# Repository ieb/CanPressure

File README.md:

# Can Pressure sender

* Emits PGN  130310L  Outside Environmental parameters and 130311L Environmental parameters with temperature, pressure, humidity from a BME280 sensor.
* Draws about 10-15mA. Uses a Attiny3224, MCP2551 CAN using an 8MHz crystal, and TJ1050.
* Attiny runs at 16MHz, but could almost certainly run slower for lower power consumption.
* PCB in pcb/ measures 66mmx27mm and is powered by 12v from NMEA2000 bus, 5V via a AMS1117, BMP280 module has its own 622K 3v regulator and level shifters.
* Needs a UDPI Programmer (I am using a UNO based programmer)
* Header for TTL Serial debugging using single character command line input.

Note, if the MCP Crystal does not match the code, when the device is plugged in it will address claim at the wrong bus frequency causing all other devices on the bus to start to fail. Check before programming that the device is running with an 8MHz MCP crystal. Change the code if using a 16MHz crystal.

# Pins and Layout

    -------------------------------------------
    |             a b c d e                   |
    | A                             AMS1117   |
    | B  TJ1050                               |
    | C                   ATTiny              |
    | D        MCP2551    3224       BME280   |
    |                                         |
    -------------------------------------------

    Debug and Programming Header
    a GND
    b 5V
    c UDPI
    d RX
    e TX

    NMEA2000 Interface
    A 12V
    B GND
    C CanL
    D CanH

# Command line on TTL

    Battery Monitor - key presses
        - 'h' or '?' to show this message
        - 's' show status
        - 'd' toggle diagnostics
        - 'r' read sensor
        - 'S' setup
        - 'R' reset
        - 'F' factory reset

* R will cause the Attiny to reboot.
* S enters setup allowing some EEPROM parameters to be set 
* F resets the EEPROM to the Factory settings
* r reads the sensors and dumps to serial.
* d toggles disagnostic output which includes CAN Frame data 
* s reports current status including packet counts, MCP Voltage and temperature.

# Developing

* Uses PlatformIO in VSCode
* Before flashing for the first time set the fuses to ensure that the chip has the correct clock. `pio run -t fuses`
* To build `pio run -t upload`

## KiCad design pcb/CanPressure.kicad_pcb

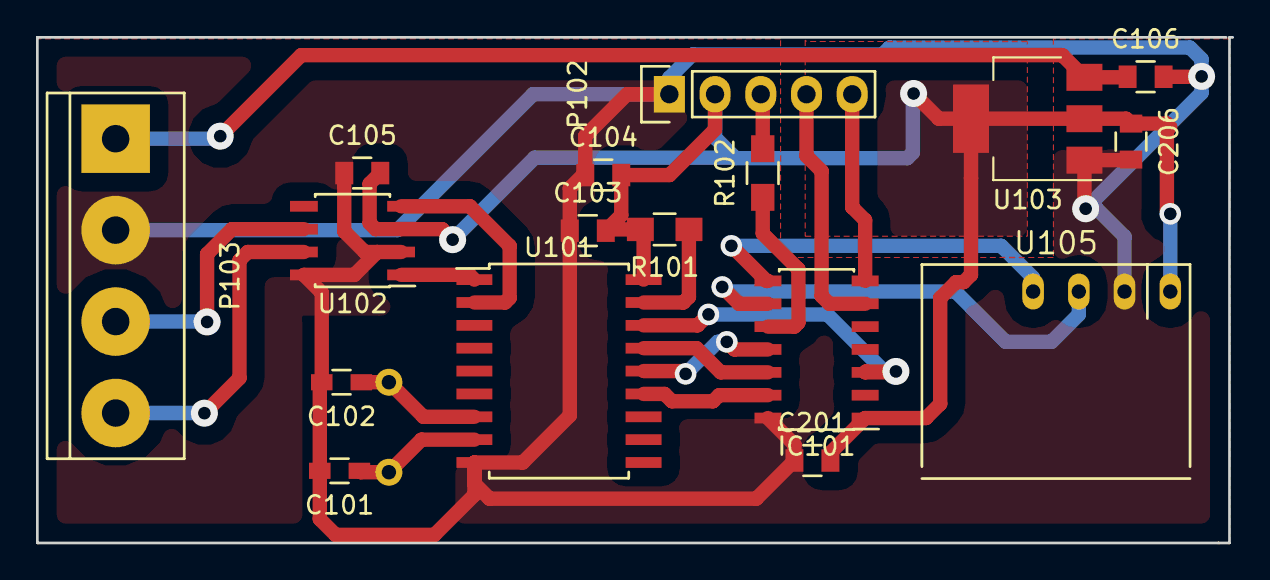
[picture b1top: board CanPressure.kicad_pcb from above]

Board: 2 copper layers, 66.4 x 28.1 mm, 18 parts (1 on the bottom side), 20 nets.

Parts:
C101, C102: 22pF; R_0603_HandSoldering
C103, C106, C206: 10uF; C_0805
C104, C105, C201: 100nF; C_0805
IC101: ATTINY3224-SS; SOIC-14_3.9x8.7mm_Pitch1.27mm
P102: CONN_5; Pin_Header_Straight_1x05
P103: CAN; bornier4
R101: 10K; R_0805_HandSoldering
R102: 270R; R_0805_HandSoldering
U101: MCP2515; SOIC-18W_7.5x11.6mm_Pitch1.27mm
U102: TJA1050; SOIC-8_3.9x4.9mm_Pitch1.27mm
U103: NCP1117ST50T3G; SOT-223-3Lead_TabPin2
U105: BMP280
X101: 8MHz; Resonator-2pin_w10.0mm_h5.0mm

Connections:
5V: C103.2, C104.2, C105.2, C201.2, C206.1, IC101.1, P102.2, R101.2, U101.18, U102.3, U103.2, U105.1
12v: C106.1, P103.1, U103.3
CANCS: IC101.3, U101.16
CANH: P103.4, U102.7
CANL: P103.3, U102.6
GND: C101.2, C102.2, C103.1, C104.1, C105.1, C106.2, C201.1, C206.2, IC101.14, P102.1, P103.2, U101.9, U102.2, U102.8, U103.1, U105.2
MISO: IC101.12, U101.15
MOSI: IC101.11, U101.14
unnamed: C101.1, U101.8, X101.1
unnamed: C102.1, U101.7, X101.2
unnamed: P102.3, R102.2
unnamed: R101.1, U101.17
unnamed: U101.1, U102.1
unnamed: U101.2, U102.4
RX: IC101.6, P102.4
SCK: IC101.13, U101.13
SCL: IC101.9, U105.3
SDA: IC101.8, U105.4
TX: IC101.7, P102.5
UDPI: IC101.10, R102.1

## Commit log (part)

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2022-07-12 Working in test harness with a MCP2515 module
2022-07-12 Added test utility
2022-07-12 Fixed bug with precision on doubles and fixed sending NMEA2000v3 messages
2022-07-13 Fixed some bugs in the setup code
2022-07-13 Fixed bug in address claim
2022-07-13 Added 3d printed case
2022-07-15 using SmallNMEA2000 as a dependency
2023-09-09 Fixed 49day overflows
